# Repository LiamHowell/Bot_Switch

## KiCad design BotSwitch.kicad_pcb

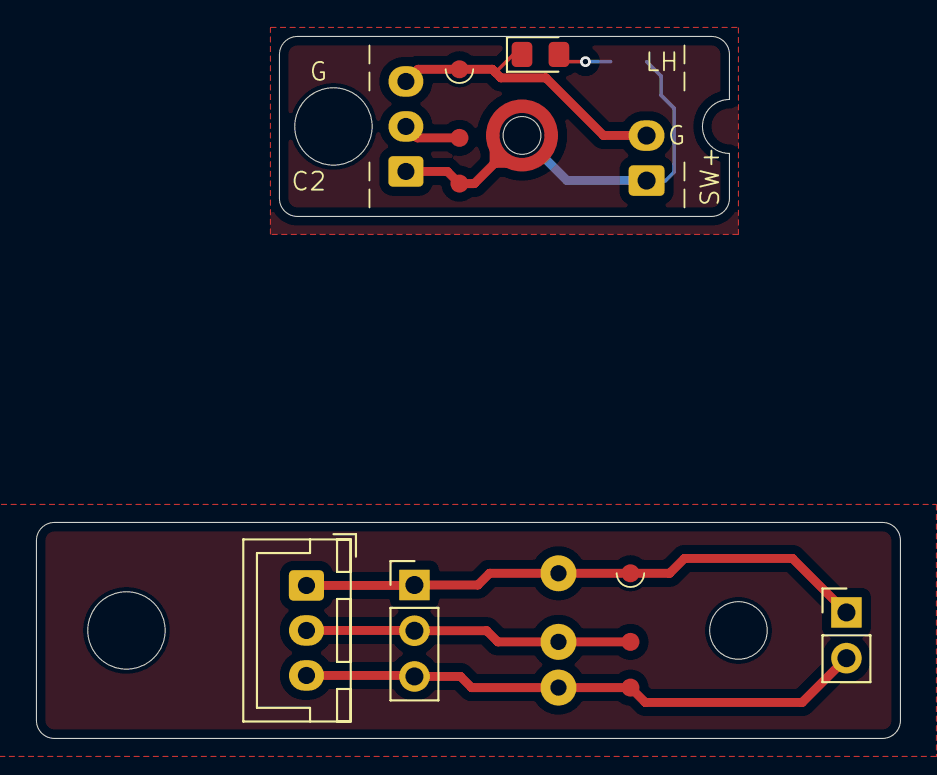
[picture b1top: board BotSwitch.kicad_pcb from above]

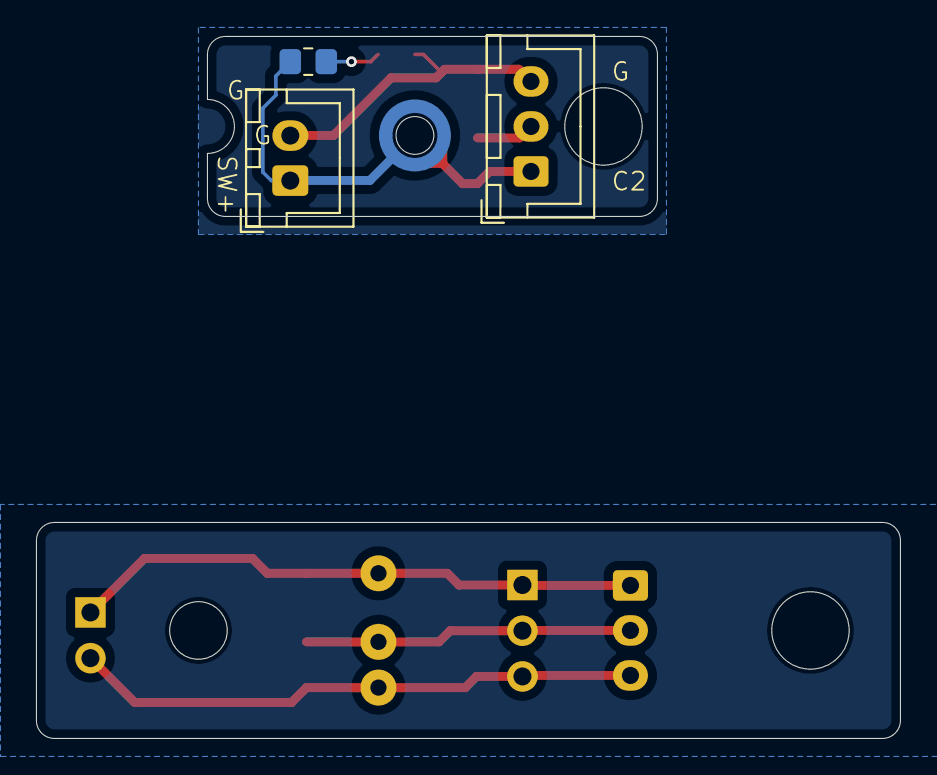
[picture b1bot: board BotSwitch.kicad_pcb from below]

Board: 2 copper layers, 48.0 x 39.0 mm, 14 parts (3 on the bottom side), 7 nets.

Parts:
D1: LED; LED_0805_2012Metric_Pad1.15x1.40mm_HandSolder
H2, H3: MountingHole; MountingHole_4.3mm_M4
H4: MountingHole; MountingHole_3.2mm_M3
J1, J7: Batt_In; JST_XH_B3B-XH-A_1x03_P2.50mm_Vertical
J2, J5: Pogo_3p; Pogo_3P
J3: to_bott; JST_XH_B2B-XH-A_1x02_P2.50mm_Vertical
J6: Conn_01x03_Pin; PinHeader_1x03_P2.54mm_Vertical
J8: Conn_01x02_Pin; PinHeader_1x02_P2.54mm_Vertical
J9: Pogo_3p; Pogo_Pin_Connection
R1: R; R_0805_2012Metric_Pad1.20x1.40mm_HandSolder
SW1: Screw Switch; Screw_Switch_M1.6

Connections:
/Cell1: J1.2, J2.2
/Cell2: J1.1, J2.3, SW1.1 (A)
/Switched_PWR: J3.1, R1.1, SW1.2 (B)
GND: D1.1 (K), J1.3, J2.1, J3.2, J5.1, J6.1, J7.1, J8.1, J9.1
unnamed: D1.2 (A), R1.2
unnamed: J5.2, J6.2, J7.2, J9.2
unnamed: J5.3, J6.3, J7.3, J8.2, J9.3

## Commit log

2025-08-28 Initial - needs lots of cleaning
2025-10-19 Final?
2025-10-19 Actual final
2025-10-19 rm lock
2025-10-22 Final final
